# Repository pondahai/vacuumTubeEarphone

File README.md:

# vacuumTubeEarphone
HA-01B vacuum tube earphone amp  
這裡是真空管耳機擴大機的kicad設計檔案

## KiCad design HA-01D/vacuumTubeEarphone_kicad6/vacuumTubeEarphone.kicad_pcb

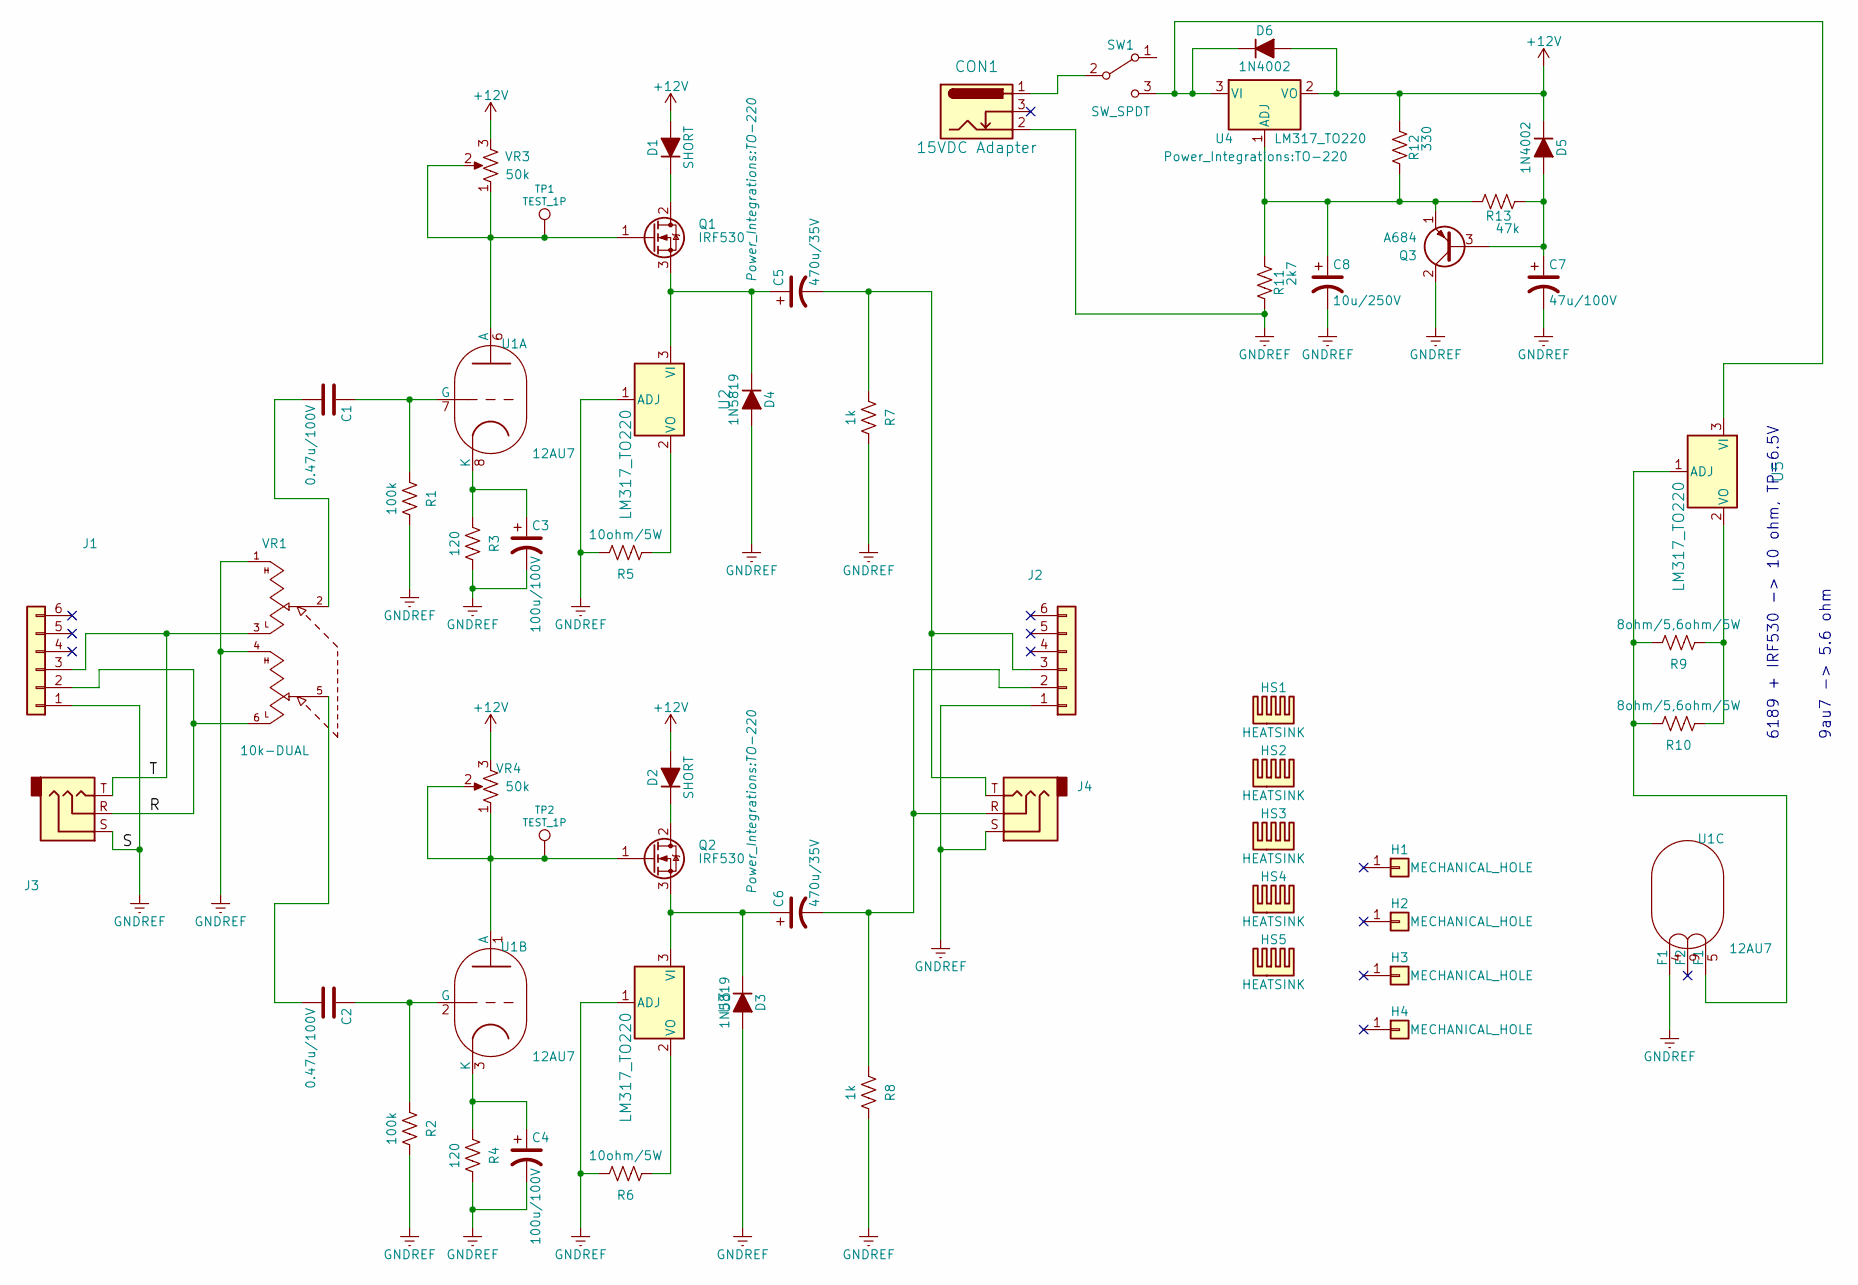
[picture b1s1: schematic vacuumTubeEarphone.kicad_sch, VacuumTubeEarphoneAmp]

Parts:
C1, C2: 0.47u/100V; C_Disc_D16.0mm_W5.0mm_P10.00mm
C3, C4: 100u/100V; CP_Radial_D10.0mm_P5.00mm
C5, C6: 470u/35V; CP_Radial_D10.0mm_P5.00mm
C7: 47u/100V; CP_Radial_D10.0mm_P5.00mm
C8: 10u/250V; CP_Radial_D10.0mm_P5.00mm
CON1: 15VDC Adapter; BARREL_JACK
D1, D2: SHORT; D_DO-15_P12.70mm_Horizontal
D3, D4: 1N5819; D_DO-15_P12.70mm_Horizontal
D5, D6: 1N4002; D_DO-15_P12.70mm_Horizontal
H1, H2, H3, H4: MECHANICAL_HOLE; MountingHole_3.2mm_M3_Pad_Via
HS1, HS2, HS3, HS4, HS5: HEATSINK; Heatsink_Stonecold_HS-132_32x14mm_2xFixation1.5mm
J1, J2, J3, J4: (no value)
Q1, Q2: IRF530; TO-220
Q3: A684; TO-92L_Inline_Wide
R1, R2: 100k; Resistor_SMD+THTuniversal_0805to2512_RM10_HandSoldering
R3, R4: 120; Resistor_SMD+THTuniversal_0805to2512_RM10_HandSoldering
R5, R6: 10ohm/5W; R_Axial_Power_L20.0mm_W6.4mm_P25.40mm
R7, R8: 1k; Resistor_SMD+THTuniversal_0805to2512_RM10_HandSoldering
R9, R10: 8ohm/5,6ohm/5W; R_Axial_Power_L20.0mm_W6.4mm_P25.40mm
R11: 2k7; Resistor_SMD+THTuniversal_0805to2512_RM10_HandSoldering
R12: 330; Resistor_SMD+THTuniversal_0805to2512_RM10_HandSoldering
R13: 47k; Resistor_SMD+THTuniversal_0805to2512_RM10_HandSoldering
SW1: SW_SPDT; SW_SPDT_90
TP1, TP2: TEST_1P; SolderWirePad_single_1mmDrill
U1: 12AU7; VALVE-ECC-83-2
U2, U3, U4, U5: LM317_TO220; TO-220
VR1: 10k-DUAL; Potentiometer_Alps_RK163_Double_Vertical
VR3, VR4: 50k; Potentiometer_Bourns_3296Y_3-8Zoll_Angular_ScrewUp

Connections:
+12V: D1.2 (A), D2.2 (A), D5.1 (K), D6.2 (A), R12.1, U4.2 (VO), VR3.3, VR4.3
/R: J1.2, J3.R, VR1.6
/T: J1.3, J3.T, VR1.3
GNDREF: C3.2, C4.2, C7.2, C8.2, CON1.2, D3.2 (A), D4.2 (A), J1.1, J2.1, J3.S, J4.S, Q3.2 (C), R1.2, R2.2, R3.2, R4.2, R5.2, R6.2, R7.2, R8.2, R11.2, U1.4 (F1), U2.1 (ADJ), U3.1 (ADJ), VR1.1, VR1.4; also elsewhere on the board
unnamed: C1.1, R1.1, U1.7 (G)
unnamed: C1.2, VR1.2
unnamed: C2.1, R2.1, U1.2 (G)
unnamed: C2.2, VR1.5
unnamed: C3.1, R3.1, U1.8 (K)
unnamed: C4.1, R4.1, U1.3 (K)
unnamed: C5.1, D4.1 (K), Q1.3 (S), U2.3 (VI)
unnamed: C5.2, J2.3, J4.T, R7.1
unnamed: C6.1, D3.1 (K), Q2.3 (S), U3.3 (VI)
unnamed: C6.2, J2.2, J4.R, R8.1
unnamed: C7.1, D5.2 (A), Q3.3 (B), R13.1
unnamed: C8.1, Q3.1 (E), R11.1, R12.2, R13.2, U4.1 (ADJ)
unnamed: CON1.1, SW1.2 (B)
unnamed: D1.1 (K), Q1.2 (D)
unnamed: D2.1 (K), Q2.2 (D)
unnamed: Q1.1 (G), TP1.1, U1.6 (A), VR3.1, VR3.2
unnamed: Q2.1 (G), TP2.1, U1.1 (A), VR4.1, VR4.2
unnamed: R5.1, U2.2 (VO)
unnamed: R6.1, U3.2 (VO)
unnamed: R9.1, R10.1, U5.2 (VO)
unnamed: R9.2, R10.2, U1.5 (F1), U5.1 (ADJ)
unnamed: D6.1 (K), SW1.3 (C), U4.3 (VI), U5.3 (VI)

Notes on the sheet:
6189 + IRF530 -> 10 ohm, TP=6.5V 9au7 -> 5.6 ohm

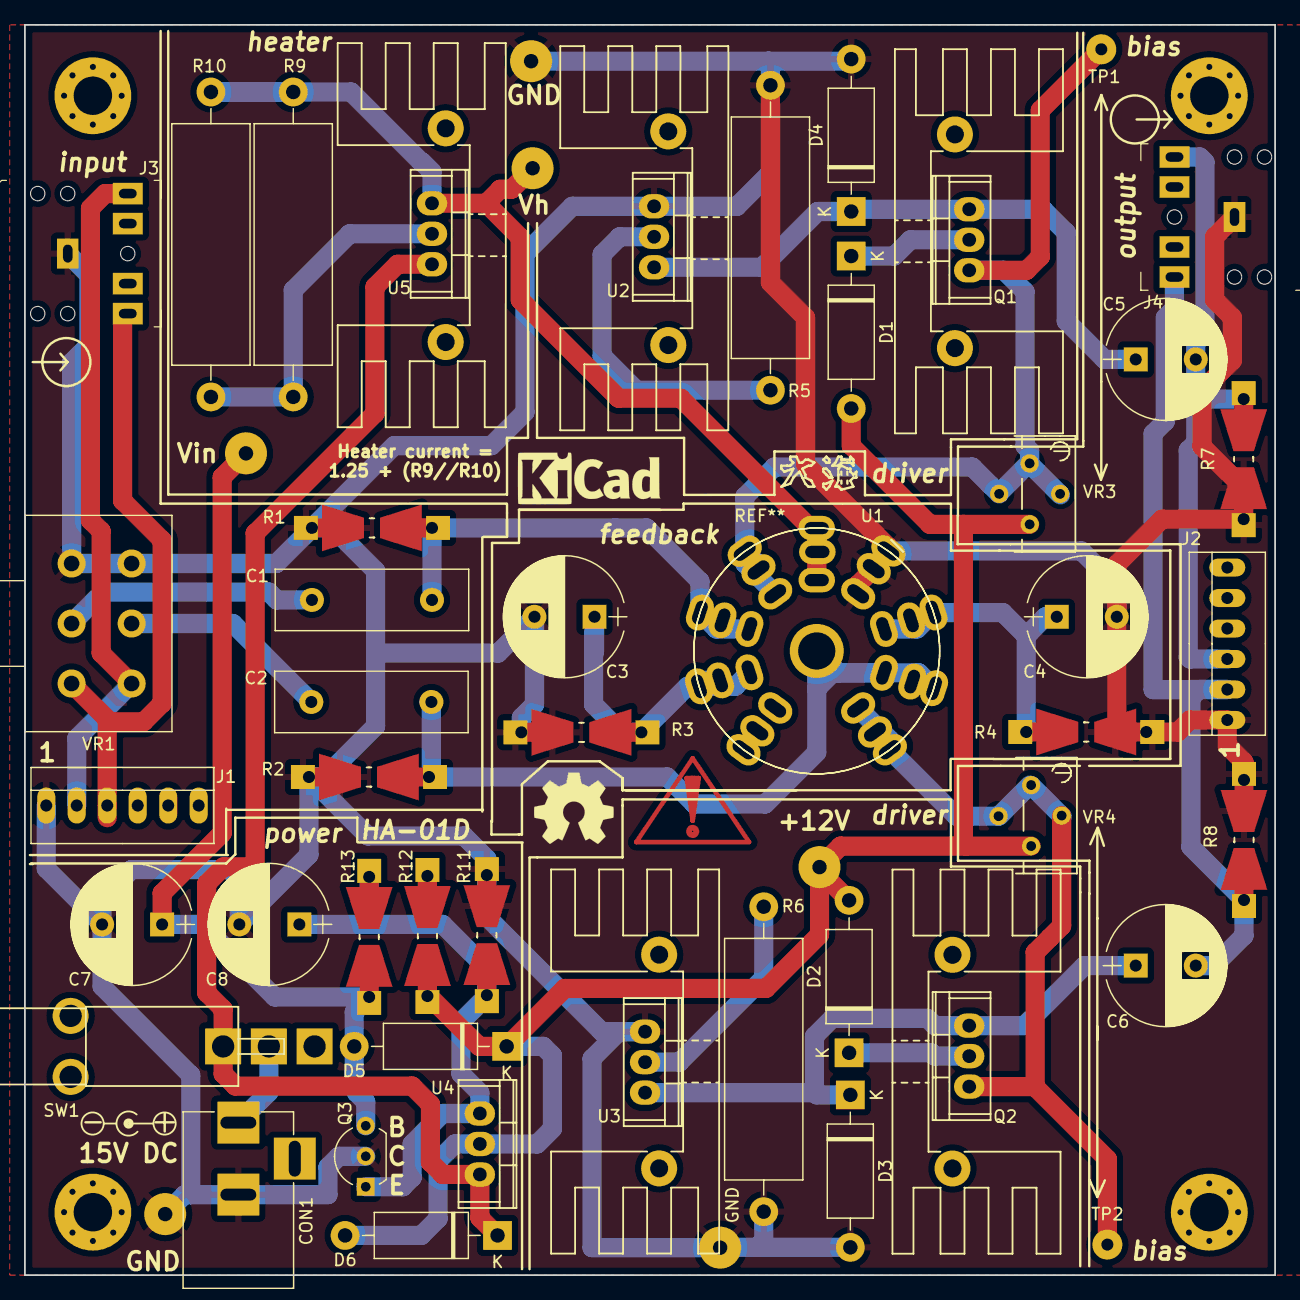
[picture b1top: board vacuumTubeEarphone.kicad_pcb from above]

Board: 2 copper layers, 104.1 x 104.1 mm, 56 parts (0 on the bottom side), 26 nets.

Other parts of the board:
GND: SolderWirePad_single_1-2mmDrill

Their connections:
GNDREF: GND.1; also elsewhere on the board

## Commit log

2017-11-27 init
2018-01-25 local google drive folder name change
2019-05-07 resync
2022-04-12 relocate folder
